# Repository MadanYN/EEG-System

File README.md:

# EEG-System
The aim of the project is to develop an ELectroencephalogram(EEG) Acquisition System that
is capable of monitoring brain activity through 24 different channels simultaneously. The system should convey the captured data in real-time to a computer over Bluetooth and the receiver should plot waveforms of all the channels. The design is inspired by the OpenBCI Cyton/Ganglion biosensing board, which is a well-known and widely used EEG system.

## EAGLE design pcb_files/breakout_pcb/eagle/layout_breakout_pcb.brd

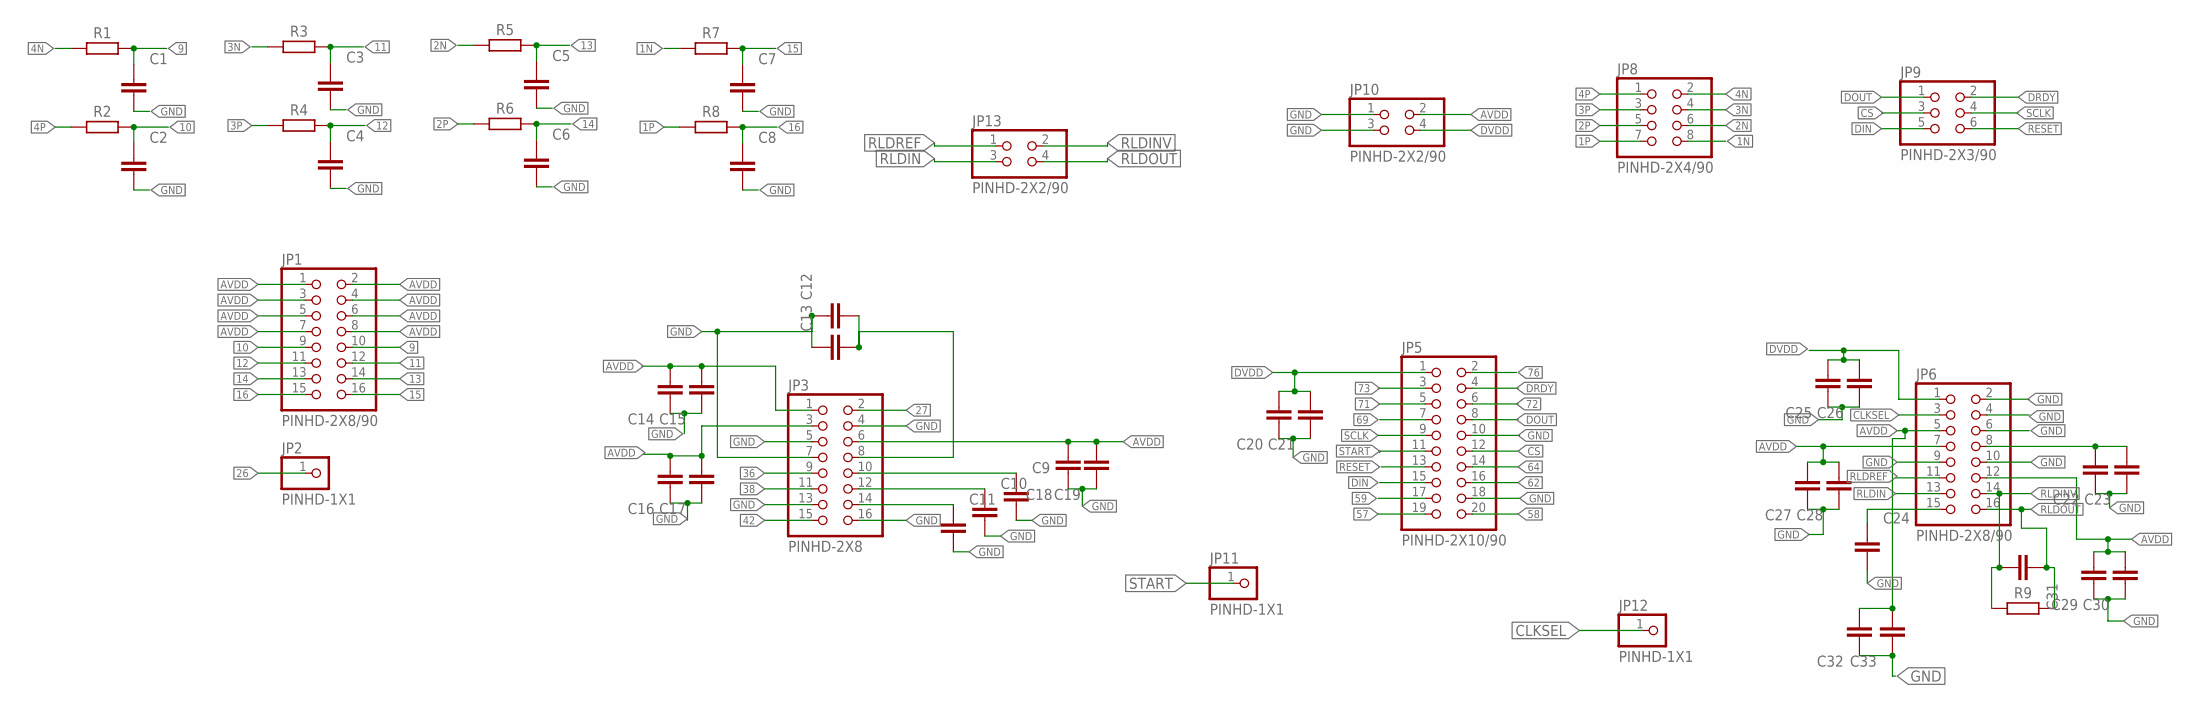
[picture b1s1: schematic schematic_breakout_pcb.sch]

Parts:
C1, C2, C3, C4, C5, C6, C7, C8, C9, C10, C11, C12, C13, C14, C15, C16, C17, C18, C19, C20, C21, C22, C23, C24, C25, C26, C27, C28, C29, C30, C31, C32, C33: C_TANTALUM-1206(3216-METRIC); CAPM3216X180
JP1, JP6: PINHD-2X8/90; 2X08/90
JP2, JP11, JP12: PINHD-1X1; 1X01
JP3: PINHD-2X8; 2X08
JP5: PINHD-2X10/90; 2X10/90
JP8: PINHD-2X4/90; 2X04/90
JP9: PINHD-2X3/90; 2X03/90
JP10, JP13: PINHD-2X2/90; 2X02/90
R1, R2, R3, R4, R5, R6, R7, R8, R9: R_CHIP-1206(3216-METRIC); RESC3216X70

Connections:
1N: JP8.8, R7.1
1P: JP8.7, R8.1
2N: JP8.6, R5.1
2P: JP8.5, R6.1
3N: JP8.4, R3.1
3P: JP8.3, R4.1
4N: JP8.2, R1.1
4P: JP8.1, R2.1
9: C1.1, JP1.10, R1.2
10: C2.1, JP1.9, R2.2
11: C3.1, JP1.12, R3.2
12: C4.1, JP1.11, R4.2
13: C5.1, JP1.14, R5.2
14: C6.1, JP1.13, R6.2
15: C7.1, JP1.16, R7.2
16: C8.1, JP1.15, R8.2
26: JP2.1
27: JP3.2
36: JP3.9
38: JP3.11
42: JP3.15
57: JP5.19
58: JP5.20
59: JP5.17
62: JP5.16
64: JP5.14
69: JP5.7
71: JP5.5
72: JP5.6
73: JP5.3
76: JP5.2
AVDD: C14.2, C15.2, C16.2, C17.2, C18.2, C19.2, C27.2, C28.2, C29.2, C30.2, C32.2, C33.2, JP1.1, JP1.2, JP1.3, JP1.4, JP1.5, JP1.6, JP1.7, JP1.8, JP3.1, JP3.3, JP3.6, JP6.5, JP6.7, JP6.12, JP10.2
CLKSEL: JP6.3, JP12.1
CS: JP5.12, JP9.3
DIN: JP5.15, JP9.5
DOUT: JP5.8, JP9.1
DRDY: JP5.4, JP9.2
DVDD: C20.2, C21.2, C25.2, C26.2, JP5.1, JP6.1, JP10.4
GND: C1.2, C2.2, C3.2, C4.2, C5.2, C6.2, C7.2, C8.2, C9.2, C10.2, C11.2, C12.1, C13.1, C14.1, C15.1, C16.1, C17.1, C18.1, C19.1, C20.1, C21.1, C22.1, C23.1, C24.2, C25.1, C26.1, C27.1, C28.1, C29.1, C30.1, C32.1, C33.1, JP3.4, JP3.5, JP3.7, JP3.13, JP3.16, JP5.10, JP5.18, JP6.2, JP6.4, JP6.6, JP6.9, JP6.10, JP10.1, JP10.3
unnamed: C9.1, JP3.10
unnamed: C10.1, JP3.12
unnamed: C11.1, JP3.14
unnamed: C12.2, C13.2, JP3.8
unnamed: C22.2, C23.2, JP6.8
unnamed: C24.1, JP6.15
RESET: JP5.13, JP9.6
RLDIN: JP6.13, JP13.3
RLDINV: C31.2, JP6.14, JP13.2, R9.1
RLDOUT: C31.1, JP6.16, JP13.4, R9.2
RLDREF: JP6.11, JP13.1
SCLK: JP5.9, JP9.4
START: JP5.11, JP11.1

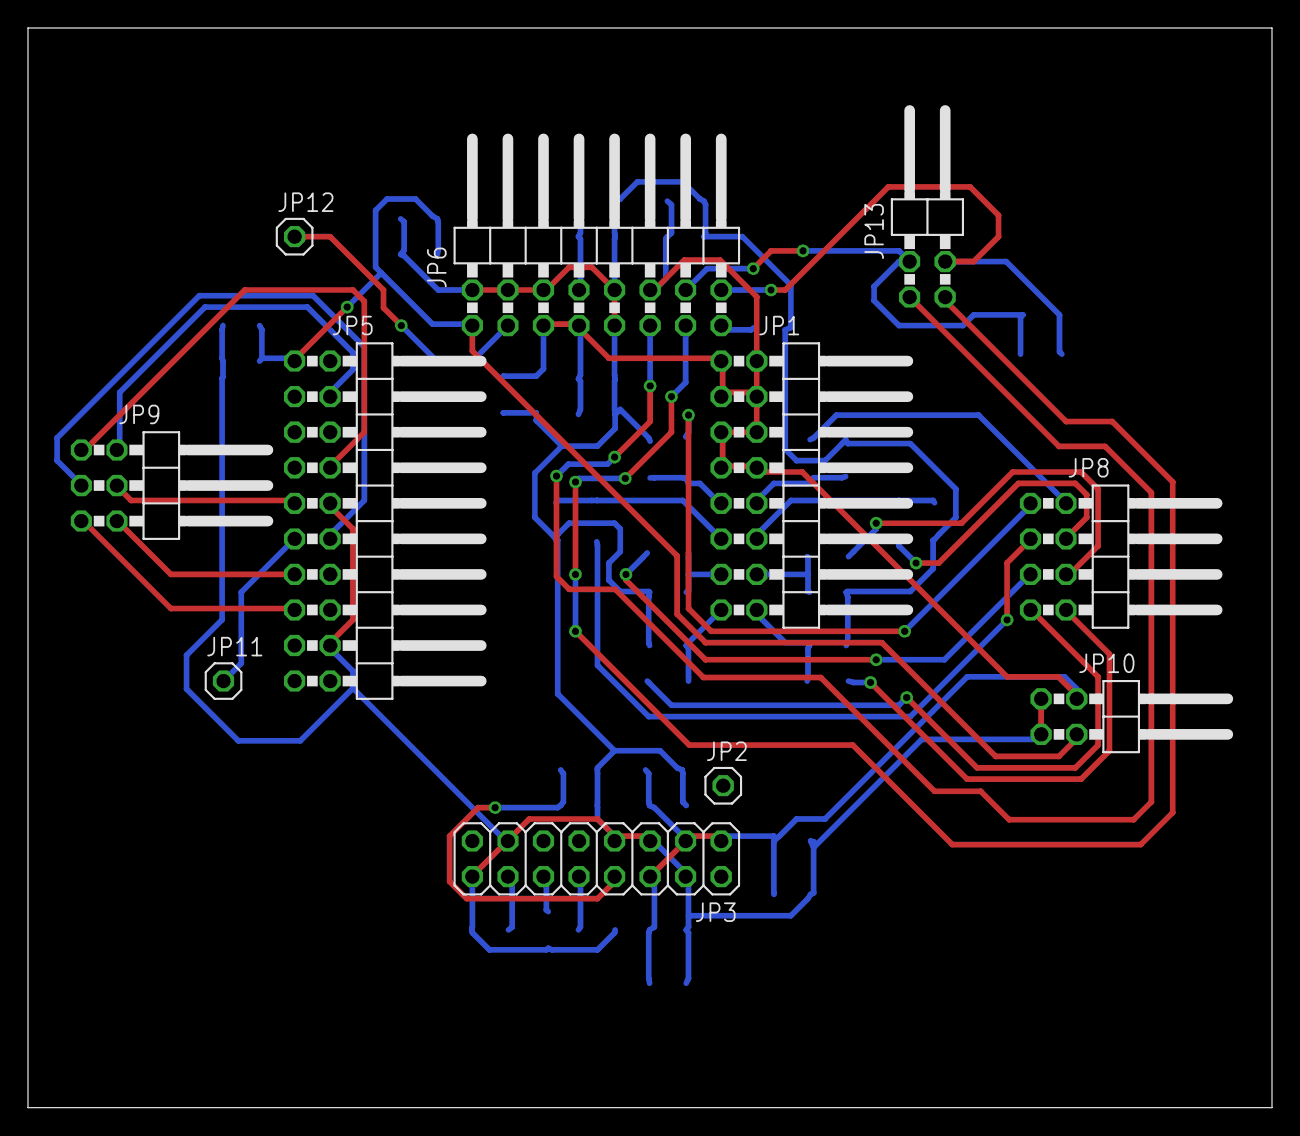
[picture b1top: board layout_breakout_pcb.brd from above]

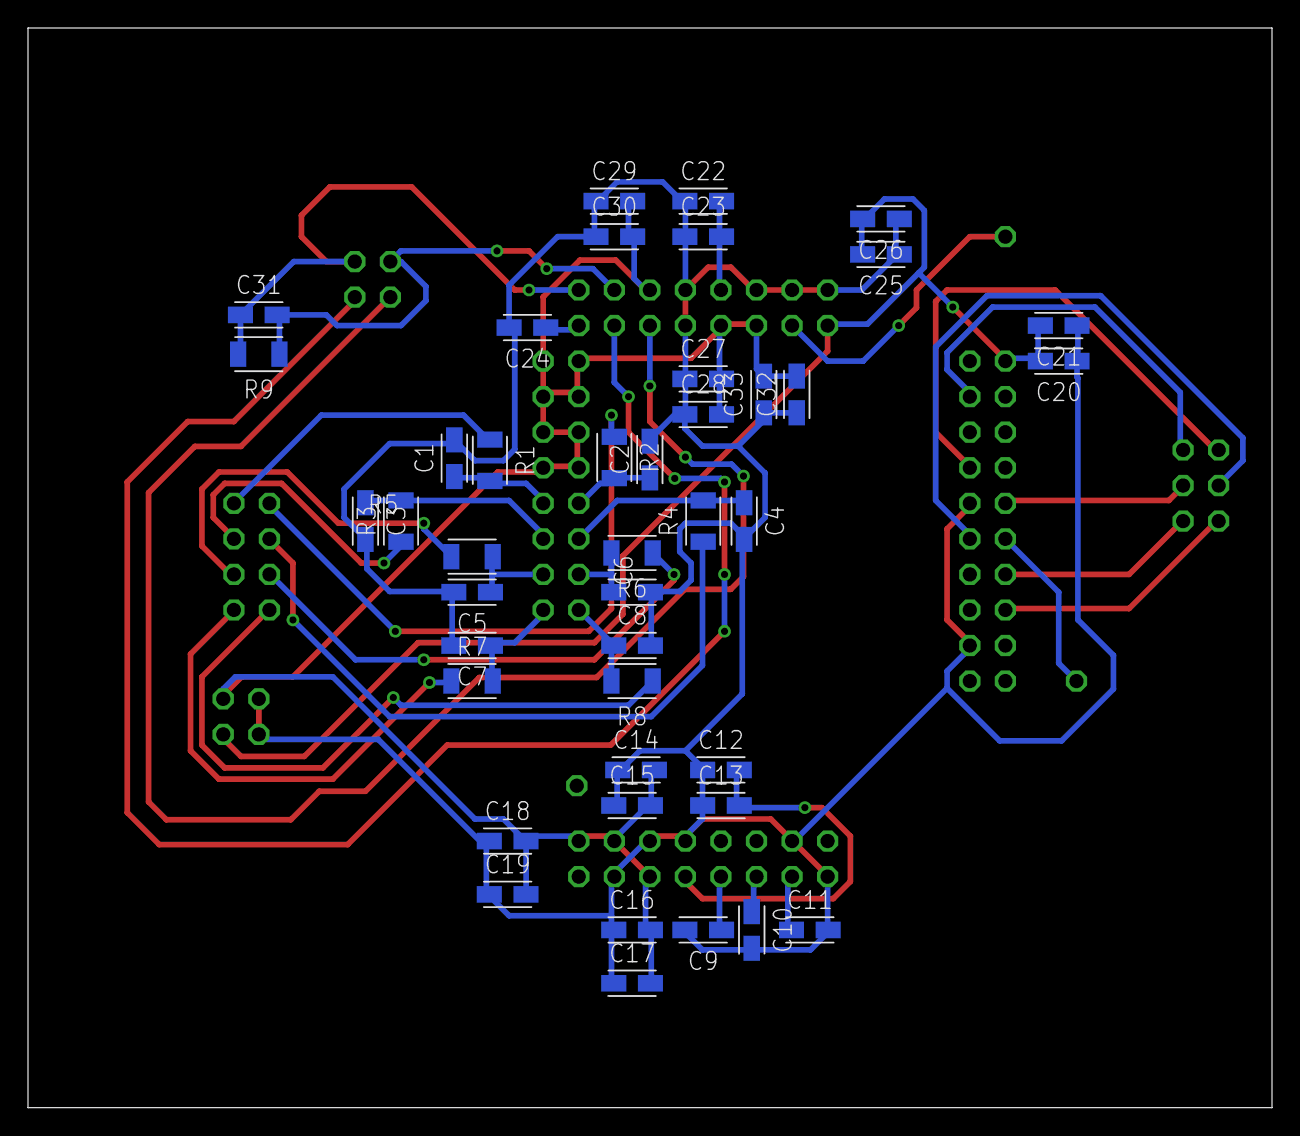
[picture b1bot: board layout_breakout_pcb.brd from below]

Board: 2 copper layers, 88.9 x 77.1 mm, 53 parts (42 on the bottom side), 37 nets.

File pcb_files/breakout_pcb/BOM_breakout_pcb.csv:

"Part";"Value";"Device";"Package";"Description";"CATEGORY";"DESCRIPTION";"MANUFACTURER";"MPN";"OPERATING_TEMP";"PART_STATUS";"RATING";"ROHS_COMPLIANT";"SERIES";"SUB-CATEGORY";"THERMALLOSS";"TOLERANCE";"TYPE";"VOLTAGE_RATING";
"C1";"";"C_TANTALUM-1206(3216-METRIC)";"CAPM3216X180";"Capacitor - Generic";"Capacitor";"";"";"";"";"";"";"";"";"";"";"";"";"";
"C2";"";"C_TANTALUM-1206(3216-METRIC)";"CAPM3216X180";"Capacitor - Generic";"Capacitor";"";"";"";"";"";"";"";"";"";"";"";"";"";
"C3";"";"C_TANTALUM-1206(3216-METRIC)";"CAPM3216X180";"Capacitor - Generic";"Capacitor";"";"";"";"";"";"";"";"";"";"";"";"";"";
"C4";"";"C_TANTALUM-1206(3216-METRIC)";"CAPM3216X180";"Capacitor - Generic";"Capacitor";"";"";"";"";"";"";"";"";"";"";"";"";"";
"C5";"";"C_TANTALUM-1206(3216-METRIC)";"CAPM3216X180";"Capacitor - Generic";"Capacitor";"";"";"";"";"";"";"";"";"";"";"";"";"";
"C6";"";"C_TANTALUM-1206(3216-METRIC)";"CAPM3216X180";"Capacitor - Generic";"Capacitor";"";"";"";"";"";"";"";"";"";"";"";"";"";
"C7";"";"C_TANTALUM-1206(3216-METRIC)";"CAPM3216X180";"Capacitor - Generic";"Capacitor";"";"";"";"";"";"";"";"";"";"";"";"";"";
"C8";"";"C_TANTALUM-1206(3216-METRIC)";"CAPM3216X180";"Capacitor - Generic";"Capacitor";"";"";"";"";"";"";"";"";"";"";"";"";"";
"C9";"";"C_TANTALUM-1206(3216-METRIC)";"CAPM3216X180";"Capacitor - Generic";"Capacitor";"";"";"";"";"";"";"";"";"";"";"";"";"";
"C10";"";"C_TANTALUM-1206(3216-METRIC)";"CAPM3216X180";"Capacitor - Generic";"Capacitor";"";"";"";"";"";"";"";"";"";"";"";"";"";
"C11";"";"C_TANTALUM-1206(3216-METRIC)";"CAPM3216X180";"Capacitor - Generic";"Capacitor";"";"";"";"";"";"";"";"";"";"";"";"";"";
"C12";"";"C_TANTALUM-1206(3216-METRIC)";"CAPM3216X180";"Capacitor - Generic";"Capacitor";"";"";"";"";"";"";"";"";"";"";"";"";"";
"C13";"";"C_TANTALUM-1206(3216-METRIC)";"CAPM3216X180";"Capacitor - Generic";"Capacitor";"";"";"";"";"";"";"";"";"";"";"";"";"";
"C14";"";"C_TANTALUM-1206(3216-METRIC)";"CAPM3216X180";"Capacitor - Generic";"Capacitor";"";"";"";"";"";"";"";"";"";"";"";"";"";
"C15";"";"C_TANTALUM-1206(3216-METRIC)";"CAPM3216X180";"Capacitor - Generic";"Capacitor";"";"";"";"";"";"";"";"";"";"";"";"";"";
"C16";"";"C_TANTALUM-1206(3216-METRIC)";"CAPM3216X180";"Capacitor - Generic";"Capacitor";"";"";"";"";"";"";"";"";"";"";"";"";"";
"C17";"";"C_TANTALUM-1206(3216-METRIC)";"CAPM3216X180";"Capacitor - Generic";"Capacitor";"";"";"";"";"";"";"";"";"";"";"";"";"";
"C18";"";"C_TANTALUM-1206(3216-METRIC)";"CAPM3216X180";"Capacitor - Generic";"Capacitor";"";"";"";"";"";"";"";"";"";"";"";"";"";
"C19";"";"C_TANTALUM-1206(3216-METRIC)";"CAPM3216X180";"Capacitor - Generic";"Capacitor";"";"";"";"";"";"";"";"";"";"";"";"";"";
"C20";"";"C_TANTALUM-1206(3216-METRIC)";"CAPM3216X180";"Capacitor - Generic";"Capacitor";"";"";"";"";"";"";"";"";"";"";"";"";"";
"C21";"";"C_TANTALUM-1206(3216-METRIC)";"CAPM3216X180";"Capacitor - Generic";"Capacitor";"";"";"";"";"";"";"";"";"";"";"";"";"";
"C22";"";"C_TANTALUM-1206(3216-METRIC)";"CAPM3216X180";"Capacitor - Generic";"Capacitor";"";"";"";"";"";"";"";"";"";"";"";"";"";
"C23";"";"C_TANTALUM-1206(3216-METRIC)";"CAPM3216X180";"Capacitor - Generic";"Capacitor";"";"";"";"";"";"";"";"";"";"";"";"";"";
"C24";"";"C_TANTALUM-1206(3216-METRIC)";"CAPM3216X180";"Capacitor - Generic";"Capacitor";"";"";"";"";"";"";"";"";"";"";"";"";"";
"C25";"";"C_TANTALUM-1206(3216-METRIC)";"CAPM3216X180";"Capacitor - Generic";"Capacitor";"";"";"";"";"";"";"";"";"";"";"";"";"";
"C26";"";"C_TANTALUM-1206(3216-METRIC)";"CAPM3216X180";"Capacitor - Generic";"Capacitor";"";"";"";"";"";"";"";"";"";"";"";"";"";
"C27";"";"C_TANTALUM-1206(3216-METRIC)";"CAPM3216X180";"Capacitor - Generic";"Capacitor";"";"";"";"";"";"";"";"";"";"";"";"";"";
"C28";"";"C_TANTALUM-1206(3216-METRIC)";"CAPM3216X180";"Capacitor - Generic";"Capacitor";"";"";"";"";"";"";"";"";"";"";"";"";"";
"C29";"";"C_TANTALUM-1206(3216-METRIC)";"CAPM3216X180";"Capacitor - Generic";"Capacitor";"";"";"";"";"";"";"";"";"";"";"";"";"";
"C30";"";"C_TANTALUM-1206(3216-METRIC)";"CAPM3216X180";"Capacitor - Generic";"Capacitor";"";"";"";"";"";"";"";"";"";"";"";"";"";
"C31";"";"C_TANTALUM-1206(3216-METRIC)";"CAPM3216X180";"Capacitor - Generic";"Capacitor";"";"";"";"";"";"";"";"";"";"";"";"";"";
"C32";"";"C_TANTALUM-1206(3216-METRIC)";"CAPM3216X180";"Capacitor - Generic";"Capacitor";"";"";"";"";"";"";"";"";"";"";"";"";"";
"C33";"";"C_TANTALUM-1206(3216-METRIC)";"CAPM3216X180";"Capacitor - Generic";"Capacitor";"";"";"";"";"";"";"";"";"";"";"";"";"";
"JP1";"PINHD-2X8/90";"PINHD-2X8/90";"2X08/90";"PIN HEADER";"CONNECTOR";"";"";"";"";"";"";"";"";"PIN-HEADER";"";"";"";"";
"JP2";"PINHD-1X1";"PINHD-1X1";"1X01";"PIN HEADER";"CONNECTOR";"";"";"";"";"";"";"";"";"PIN-HEADER";"";"";"";"";
"JP3";"PINHD-2X8";"PINHD-2X8";"2X08";"PIN HEADER";"CONNECTOR";"";"";"";"";"";"";"";"";"PIN-HEADER";"";"";"";"";
"JP5";"PINHD-2X10/90";"PINHD-2X10/90";"2X10/90";"PIN HEADER";"CONNECTOR";"";"";"";"";"";"";"";"";"PIN-HEADER";"";"";"";"";
"JP6";"PINHD-2X8/90";"PINHD-2X8/90";"2X08/90";"PIN HEADER";"CONNECTOR";"";"";"";"";"";"";"";"";"PIN-HEADER";"";"";"";"";
"JP8";"PINHD-2X4/90";"PINHD-2X4/90";"2X04/90";"PIN HEADER";"CONNECTOR";"";"";"";"";"";"";"";"";"PIN-HEADER";"";"";"";"";
"JP9";"PINHD-2X3/90";"PINHD-2X3/90";"2X03/90";"PIN HEADER";"CONNECTOR";"";"";"";"";"";"";"";"";"PIN-HEADER";"";"";"";"";
"JP10";"PINHD-2X2/90";"PINHD-2X2/90";"2X02/90";"PIN HEADER";"CONNECTOR";"";"";"";"";"";"";"";"";"PIN-HEADER";"";"";"";"";
"JP11";"PINHD-1X1";"PINHD-1X1";"1X01";"PIN HEADER";"CONNECTOR";"";"";"";"";"";"";"";"";"PIN-HEADER";"";"";"";"";
"JP12";"PINHD-1X1";"PINHD-1X1";"1X01";"PIN HEADER";"CONNECTOR";"";"";"";"";"";"";"";"";"PIN-HEADER";"";"";"";"";
"JP13";"PINHD-2X2/90";"PINHD-2X2/90";"2X02/90";"PIN HEADER";"CONNECTOR";"";"";"";"";"";"";"";"";"PIN-HEADER";"";"";"";"";
"R1";"";"R_CHIP-1206(3216-METRIC)";"RESC3216X70";"Resistor Fixed - Generic";"Resistor";"";"";"";"";"";"";"";"";"Fixed";"";"";"";"";
"R2";"";"R_CHIP-1206(3216-METRIC)";"RESC3216X70";"Resistor Fixed - Generic";"Resistor";"";"";"";"";"";"";"";"";"Fixed";"";"";"";"";
"R3";"";"R_CHIP-1206(3216-METRIC)";"RESC3216X70";"Resistor Fixed - Generic";"Resistor";"";"";"";"";"";"";"";"";"Fixed";"";"";"";"";
"R4";"";"R_CHIP-1206(3216-METRIC)";"RESC3216X70";"Resistor Fixed - Generic";"Resistor";"";"";"";"";"";"";"";"";"Fixed";"";"";"";"";
"R5";"";"R_CHIP-1206(3216-METRIC)";"RESC3216X70";"Resistor Fixed - Generic";"Resistor";"";"";"";"";"";"";"";"";"Fixed";"";"";"";"";
"R6";"";"R_CHIP-1206(3216-METRIC)";"RESC3216X70";"Resistor Fixed - Generic";"Resistor";"";"";"";"";"";"";"";"";"Fixed";"";"";"";"";
"R7";"";"R_CHIP-1206(3216-METRIC)";"RESC3216X70";"Resistor Fixed - Generic";"Resistor";"";"";"";"";"";"";"";"";"Fixed";"";"";"";"";
"R8";"";"R_CHIP-1206(3216-METRIC)";"RESC3216X70";"Resistor Fixed - Generic";"Resistor";"";"";"";"";"";"";"";"";"Fixed";"";"";"";"";
"R9";"";"R_CHIP-1206(3216-METRIC)";"RESC3216X70";"Resistor Fixed - Generic";"Resistor";"";"";"";"";"";"";"";"";"Fixed";"";"";"";"";

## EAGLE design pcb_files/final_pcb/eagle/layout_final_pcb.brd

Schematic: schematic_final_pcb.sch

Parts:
C1, C2, C6, C8, C9, C11, C13, C16, C20, C23, C27, C29, C32, C37, C40, C44, C46, C49, C53, C56, C57, C59, C62, C65, C70, C72, C75, C78, C79, C80, C82, C88, C90, C92, C95, C99, C105, C111, C112, C113, C116, C117, C123, C124, C133, C134, C135, C137, C143, C150, C151, C155, C157, C159, C161, C163, C165, C167, C169, C171, C173, C175, C177, C179, C181, C183, C185, C187, C189, C191, C193, C195, C197, C199, C201, C203, C205, C207, C209, C211, C213, C215, C217, C219, C221, C223, C225, C227, C229, C231, C233, C235, C237, C239, C241, C243, C245, C247, C250, C252, C254, C256, C258: 0.1uF; CAPC2012X110
C3, C4, C10, C12, C15, C17, C19, C22, C26, C28, C31, C33, C34, C36, C38, C39, C43, C45, C48, C50, C52, C55, C58, C61, C63, C66, C69, C71, C74, C76, C81, C91, C97, C118, C119, C120, C121, C125, C138, C139, C140, C141, C142, C144, C145, C146, C147, C148, C149, C152, C156, C158, C160, C162, C164, C166, C168, C170, C172, C174, C176, C178, C180, C182, C184, C186, C188, C190, C192, C194, C196, C198, C200, C202, C204, C206, C208, C210, C212, C214, C216, C218, C220, C222, C224, C226, C228, C230, C232, C234, C236, C238, C240, C242, C244, C246, C248, C251, C253, C255, C257, C259: 1uF; CAPC2012X110
C5, C14, C18, C30, C35, C47, C51, C60, C64, C73, C77, C85, C86: 10uF; CAP_293D-A_VSS
C7, C25, C42, C68, C84, C94: 100pF; CAPC1608X85
C21, C87, C89, C96, C100, C132: 2.2uF; CAPC1608X85
C24, C41, C54, C67, C83, C93: 1.5nF; CAPC1608X85
C98: 0.01uF; CAPC2012X110
C101, C102, C122, C136, C153, C154: 22uF; CAPM3216X180
C103, C104, C106, C107, C108, C109, C110, C126, C127, C128, C129, C130, C131: CKCL44X7R1H102M085AACKCL44_TDK-L; CKCL44_TDK-L
C114, C115: 15pF; CAPC1608X85
CR1: BAT85,113DO-34_NEX; DO-34_NEX
FB1, FB2, FB3, FB4, FB5, FB6, FB7, FB8, FB9, FB10, FB11, FB12, FB13, FB14: FERRITE_BEAD; BEADC1608X95N
J1: 3A/250V; B2B-XH-A
JP1, JP5: PINHD-1X6/90; 1X06/90
JP3, JP16, JP18: PINHD-2X3/90; 2X03/90
JP4, JP6: PINHD-1X8/90; 1X08/90
JP7: PINHD-1X7/90; 1X07/90
JP9, JP11, JP13, JP14, JP15, JP17: PINHD-2X4/90; 2X04/90
JP10: PINHD-1X4; 1X04
JP12: PINHD-1X1; 1X01
JP19, JP20, JP21, JP22, JP23, JP24: PINHD-1X2/90; 1X02/90
R1: 1k; RESC1608X60
R2: 470k; RESC1608X60
R3, R4, R5, R6, R7, R8, R10: 1M; RESC1608X60
R9: 10k; RESC1608X60
RN1, RN2, RN3, RN4, RN5, RN6, RN7, RN8, RN9, RN10, RN11, RN12, RN13: CAY16-2201F4LF; RESCAF80P320X160X60-8N
S2: B3U-X000B3U3000P(M)-B3000P(M)-B; B3U-3000P(M)-B
TP1, TP4, TP5, TP7, TP8, TP9, TP10, TP16, TP18, TP19, TP20, TP21, TP22, TP23, TP24, TP25, TP26, TP27, TP28, TP29, TP30: TP; 1X01
TPCS1, TPCS2, TPCS3, TPCS4, TPCS5, TPCS6, TPCS7, TPCS8, TPCS9: TP; 1X01
TPRAW: TP; 1X01
U1, U2, U3, U4, U5, U7: ADS1194CPAG; QFP50P1200X1200X120-64N
U6: LM2664M6; SOT95P280X145-6N
U8: PIC32MX250F128D-I_PT; QFP44_10X10MC
U9: MCP1754T-5002E/MC; SON50P200X300X100-9N
U10: TPS72325QDBVRQ1; SOT95P280X145-5N
U11: TLV70012QDCKRQ1; SOT65P210X110-5N
U13, U14, U15, U16, U17, U18, U19, U20, U21, U22, U23, U24, U25: TPD4E1B06DRLR; SOT50P160X60-6N
U26: LIS3DHHTRQFN_ICLX_STM; QFN_ICLX_STM
XTAL1: 8M; XTALRR488W45L1150T500H350B

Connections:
1N: JP17.7, RN1.3, U13.1 (IO1)
1P: JP17.8, RN1.4, U13.3 (IO2)
2N: JP17.5, RN1.1, U13.4 (IO3)
2P: JP17.6, RN1.2, U13.6 (IO4)
3N: JP17.3, RN2.3, U14.1 (IO1)
3P: JP17.4, RN2.4, U14.3 (IO2)
4N: JP17.1, RN2.1, U14.4 (IO3)
4P: JP17.2, RN2.2, U14.6 (IO4)
5N: JP18.5, RN3.3, U15.1 (IO1)
5P: JP18.6, RN3.4, U15.3 (IO2)
6N: JP18.3, RN3.1, U15.4 (IO3)
6P: JP18.4, RN3.2, U15.6 (IO4)
7N: JP18.1, RN4.3, U16.1 (IO1)
7P: JP18.2, RN4.4, U16.3 (IO2)
8N: JP9.7, RN4.1, U16.4 (IO3)
8P: JP9.8, RN4.2, U16.6 (IO4)
9N: JP15.7, RN5.3, U17.1 (IO1)
9P: JP15.8, RN5.4, U17.3 (IO2)
10N: JP15.5, RN5.1, U17.4 (IO3)
10P: JP15.6, RN5.2, U17.6 (IO4)
11N: JP15.3, RN6.3, U18.1 (IO1)
11P: JP15.4, RN6.4, U18.3 (IO2)
12N: JP15.1, RN6.1, U18.4 (IO3)
12P: JP15.2, RN6.2, U18.6 (IO4)
13N: JP16.5, RN7.3, U19.1 (IO1)
13P: JP16.6, RN7.4, U19.3 (IO2)
14N: JP16.3, RN7.1, U19.4 (IO3)
14P: JP16.4, RN7.2, U19.6 (IO4)
15N: JP16.1, RN8.3, U20.1 (IO1)
15P: JP16.2, RN8.4, U20.3 (IO2)
16N: JP11.7, RN8.1, U20.4 (IO3)
16P: JP11.8, RN8.2, U20.6 (IO4)
17N: JP14.7, RN9.3, U21.1 (IO1)
17P: JP14.8, RN9.4, U21.3 (IO2)
18N: JP14.5, RN9.1, U21.4 (IO3)
18P: JP14.6, RN9.2, U21.6 (IO4)
19N: JP14.3, RN10.3, U22.1 (IO1)
19P: JP14.4, RN10.4, U22.3 (IO2)
20N: JP14.1, RN10.1, U22.4 (IO3)
20P: JP14.2, RN10.2, U22.6 (IO4)
21N: JP3.5, RN11.3, U23.1 (IO1)
21P: JP3.6, RN11.4, U23.3 (IO2)
22N: JP3.3, RN11.1, U23.4 (IO3)
22P: JP3.4, RN11.2, U23.6 (IO4)
23N: JP3.1, RN12.3, U24.1 (IO1)
23P: JP3.2, RN12.4, U24.3 (IO2)
24N: JP13.7, RN12.1, U24.4 (IO3)
24P: JP13.8, RN12.2, U24.6 (IO4)
-RAW: C51.2, C89.1, U6.2 (OUT), U10.1 (IN), U10.2 (EN)
AGND: C1.2, C6.2, C11.2, C12.2, C18.1, C19.2, C20.2, C27.2, C28.2, C35.1, C36.2, C37.2, C38.2, C44.2, C45.2, C51.1, C52.2, C53.2, C57.2, C58.2, C65.2, C66.2, C70.2, C71.2, C78.2, C79.2, C80.2, C87.2, C89.2, C90.2, C95.2, C96.2, C97.2, C98.2, C99.2, C100.2, C103.1, C103.2, C103.3, C103.4, C104.1, C104.2, C104.3, C104.4, C105.2, C106.1, C106.2, C106.3, C106.4, C107.1, C107.2, C107.3, C107.4, C108.1, C108.2, C108.3, C108.4, C109.1, C109.2, C109.3, C109.4, C110.1, C110.2, C110.3, C110.4, C112.1, C116.2, C118.2, C120.2, C123.2, C124.2, C125.2, C126.1, C126.2, C126.3, C126.4, C127.1, C127.2, C127.3, C127.4, C128.1, C128.2, C128.3, C128.4, C129.1, C129.2, C129.3, C129.4, C130.1, C130.2, C130.3, C130.4, C131.1, C131.2, C131.3, C131.4, C131.6, C131.7, C131.8, C132.2, C133.2, C134.2, C135.2, C137.2, C138.2, C139.2, C140.2, C141.2, C142.2, C143.2, C144.2, C145.2, C146.2, C147.2, C148.2, C149.2, C152.2, C155.2, C156.2, C157.2, C158.2, C159.2, C160.2, C161.2, C162.2, C163.2, C164.2, C165.2, C166.2, C169.2, C170.2, C171.2, C172.2, C173.2, C174.2, C175.2, C176.2, C177.2, C178.2, C179.2, C180.2, C181.2, C182.2, C183.2, C184.2, C185.2, C186.2, C187.2, C188.2, C189.2, C190.2, C191.2, C192.2, C193.2, C194.2, C195.2, C196.2, C197.2, C198.2, C199.2, C200.2, C201.2, C202.2, C203.2, C204.2, C205.2, C206.2, C207.2, C208.2, C209.2, C210.2, C211.2, C212.2, C213.2, C214.2, C215.2, C216.2, C217.2, C218.2, C219.2, C220.2, C221.2, C222.2, C223.2, C224.2, C225.2, C226.2, C227.2, C228.2, C229.2, C230.2, C231.2, C232.2, C233.2, C234.2, C235.2, C236.2, C237.2, C238.2, C239.2, C240.2, C241.2, C242.2, C243.2, C244.2, C245.2, C246.2, C247.2, C248.2, FB1.1, FB2.1, FB3.1, FB4.1, FB5.1, FB6.1, FB7.1, FB8.1, FB9.1, FB10.1, FB11.1, FB12.1, FB13.1, FB14.1, J1.2, JP5.4, JP7.3, JP9.3, JP9.4, JP11.3, JP11.4, JP13.3, JP13.4, RN13.2, RN13.3, RN13.4, RN13.5, RN13.6, RN13.7, TP18.1, TP19.1, TP20.1, TP21.1, U6.1 (GND), U8.16 (AVSS), U9.4 (GND), U10.3 (GND), U11.2 (GND), U13.2 (GND), U14.2 (GND), U15.2 (GND), U16.2 (GND), U17.2 (GND), U18.2 (GND), U19.2 (GND), U20.2 (GND), U21.2 (GND), U22.2 (GND), U23.2 (GND), U24.2 (GND), U25.2 (GND), U25.4 (IO3)
AVDD: C1.1, C11.1, C12.1, C18.2, C27.1, C28.1, C44.1, C45.1, C57.1, C58.1, C70.1, C71.1, C100.1, C116.1, C120.1, C133.1, C134.1, C135.1, C137.1, C143.1, C144.1, C145.1, C146.1, C147.1, C148.1, C149.1, C159.1, C160.1, C161.1, C162.1, C163.1, C164.1, C165.1, C166.1, C209.1, C210.1, C211.1, C212.1, C213.1, C214.1, C215.1, C216.1, C217.1, C218.1, C219.1, C220.1, C221.1, C222.1, C223.1, C224.1, C225.1, C226.1, C227.1, C228.1, C229.1, C230.1, C231.1, C232.1, C233.1, C234.1, C235.1, C236.1, C237.1, C238.1, C239.1, C240.1, C241.1, C242.1, C243.1, C244.1, C245.1, C246.1, C247.1, C248.1, JP9.1, JP9.2, JP11.1, JP11.2, JP13.1, JP13.2, TP1.1, U1.1 (IN8N), U1.2 (IN8P), U1.3 (IN7N), U1.4 (IN7P), U1.5 (IN6N), U1.6 (IN6P), U1.7 (IN5N), U1.8 (IN5P), U1.19 (AVDD), U1.21 (AVDD), U1.22 (AVDD), U1.54 (AVDD1), U1.56 (AVDD), U1.59 (AVDD), U2.1 (IN8N), U2.2 (IN8P), U2.3 (IN7N), U2.4 (IN7P), U2.5 (IN6N), U2.6 (IN6P), U2.7 (IN5N), U2.8 (IN5P), U2.19 (AVDD), U2.21 (AVDD), U2.22 (AVDD), U2.54 (AVDD1), U2.56 (AVDD), U2.59 (AVDD), U3.1 (IN8N), U3.2 (IN8P), U3.3 (IN7N), U3.4 (IN7P), U3.5 (IN6N), U3.6 (IN6P), U3.7 (IN5N), U3.8 (IN5P), U3.19 (AVDD), U3.21 (AVDD), U3.22 (AVDD), U3.54 (AVDD1), U3.56 (AVDD), U3.59 (AVDD), U4.1 (IN8N), U4.2 (IN8P), U4.3 (IN7N), U4.4 (IN7P), U4.5 (IN6N), U4.6 (IN6P), U4.7 (IN5N), U4.8 (IN5P), U4.19 (AVDD), U4.21 (AVDD), U4.22 (AVDD), U4.54 (AVDD1), U4.56 (AVDD), U4.59 (AVDD), U5.1 (IN8N), U5.2 (IN8P), U5.3 (IN7N), U5.4 (IN7P), U5.5 (IN6N), U5.6 (IN6P), U5.7 (IN5N), U5.8 (IN5P), U5.19 (AVDD), U5.21 (AVDD), U5.22 (AVDD), U5.54 (AVDD1), U5.56 (AVDD), U5.59 (AVDD), U7.1 (IN8N), U7.2 (IN8P), U7.3 (IN7N), U7.4 (IN7P), U7.5 (IN6N), U7.6 (IN6P), U7.7 (IN5N), U7.8 (IN5P), U7.19 (AVDD), U7.21 (AVDD), U7.22 (AVDD), U7.54 (AVDD1), U7.56 (AVDD), U7.59 (AVDD), U11.5 (OUT), U25.3 (IO2)
AVSS: C2.1, C3.2, C5.2, C6.1, C7.2, C8.2, C10.2, C13.1, C14.2, C15.2, C16.2, C17.2, C19.1, C20.1, C25.2, C26.2, C29.1, C30.2, C31.2, C32.2, C33.2, C34.2, C35.2, C36.1, C37.1, C38.1, C42.2, C43.2, C46.1, C47.2, C48.2, C49.2, C50.2, C52.1, C53.1, C59.1, C60.2, C61.2, C62.2, C63.2, C65.1, C66.1, C68.2, C69.2, C72.1, C73.2, C74.2, C75.2, C76.2, C78.1, C79.1, C80.1, C84.2, C90.1, C94.2, C95.1, C96.1, C97.1, C99.1, C101.2, C102.2, C105.1, C118.1, C119.2, C121.2, C122.2, C123.1, C124.1, C125.1, C136.2, C138.1, C139.1, C140.1, C141.1, C142.1, C152.1, C153.2, C154.2, C155.1, C156.1, C157.1, C158.1, C169.1, C170.1, C171.1, C172.1, C173.1, C174.1, C175.1, C176.1, C177.1, C178.1, C179.1, C180.1, C181.1, C182.1, C183.1, C184.1, C185.1, C186.1, C187.1, C188.1, C189.1, C190.1, C191.1, C192.1, C193.1, C194.1, C195.1, C196.1, C197.1, C198.1, C199.1, C200.1, C201.1, C202.1, C203.1, C204.1, C205.1, C206.1, C207.1, C208.1, TP8.1, U1.20 (AVSS), U1.23 (AVSS), U1.25 (VREFN), U1.32 (AVSS), U1.53 (AVSS1), U1.57 (AVSS), U1.58 (AVSS), U2.20 (AVSS), U2.23 (AVSS), U2.25 (VREFN), U2.32 (AVSS), U2.53 (AVSS1), U2.57 (AVSS), U2.58 (AVSS), U3.20 (AVSS), U3.23 (AVSS), U3.25 (VREFN), U3.32 (AVSS), U3.53 (AVSS1), U3.57 (AVSS), U3.58 (AVSS), U4.20 (AVSS), U4.23 (AVSS), U4.25 (VREFN), U4.32 (AVSS), U4.53 (AVSS1), U4.57 (AVSS), U4.58 (AVSS), U5.20 (AVSS), U5.23 (AVSS), U5.25 (VREFN), U5.32 (AVSS), U5.53 (AVSS1), U5.57 (AVSS), U5.58 (AVSS), U7.20 (AVSS), U7.23 (AVSS), U7.25 (VREFN), U7.32 (AVSS), U7.53 (AVSS1), U7.57 (AVSS), U7.58 (AVSS), U10.4 (OUT), U25.1 (IO1)
BIAS: JP9.5, JP9.6, JP11.5, JP11.6, JP13.5, JP13.6, RN13.1, U25.6 (IO4)
BIAS_ESD: C131.5, RN13.8, U1.60 (RLDREF), U2.60 (RLDREF), U3.60 (RLDREF), U4.60 (RLDREF), U5.60 (RLDREF), U7.60 (RLDREF)
BOOT_EN: R2.2, S2.1, U8.33 (SOSCI/RPB4/RB4)
CLK: JP6.6, JP12.1, U1.37 (CLK), U2.37 (CLK), U3.37 (CLK), U4.37 (CLK), U5.37 (CLK), U7.37 (CLK)
CS1: TPCS1.1, U4.39 (!CS), U8.15 (AN9/C3INA/RPB15/SCK2/CTED6/PMCS1/RB15)
CS2: TPCS2.1, U7.39 (!CS), U8.1 (RPB9/SDA1/CTED4/PMD3/RB9)
CS3: TPCS3.1, U1.39 (!CS), U8.44 (RPB8/SCL1/CTED10/PMD4/RB8)
CS4: TPCS4.1, U2.39 (!CS), U8.43 (RPB7/CTED3/PMD5/INT0/RB7)
CS5: TPCS5.1, U3.39 (!CS), U8.21 (PGED1/AN2/C1IND/C2INB/C3IND/RPB0/PMD0/R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)
CS6: TPCS6.1, U5.39 (!CS), U8.22 (PGEC1/AN3/C1INC/C2INA/RPB1/CTED12/PMD1/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)
CS7: TPCS7.1, U8.34 (SOSCO/RPA4/T1CK/CTED9/RA4), U26.4 (CS)
CS8: JP7.1, TPCS8.1, U8.35 (TDI/RPA9/PMA9/RA9)
CS9: JP6.8, TPCS9.1, U8.38 (RPC5/PMA3/RC5)
DGND: C4.2, C9.2, C21.2, C22.2, C23.2, C39.2, C40.2, C55.2, C56.2, C77.1, C81.2, C82.2, C85.2, C86.1, C88.2, C91.2, C92.2, C111.2, C113.2, C114.2, C115.2, C117.1, C150.2, C151.2, C167.2, C168.2, C250.2, C251.2, C252.2, C253.2, C254.2, C255.2, C256.2, C257.2, C258.2, C259.2, FB1.2, FB2.2, FB3.2, FB4.2, FB5.2, FB6.2, FB7.2, FB8.2, FB9.2, FB10.2, FB11.2, FB12.2, FB13.2, FB14.2, JP4.5, JP6.2, JP7.6, R2.1, TP22.1, TP23.1, TP24.1, TP25.1, TP26.1, TP27.1, TP28.1, TP29.1, U1.31 (RESV1), U1.33 (DGND), U1.41 (DAISY_IN), U1.49 (DGND), U1.51 (DGND), U2.31 (RESV1), U2.33 (DGND), U2.41 (DAISY_IN), U2.49 (DGND), U2.51 (DGND), U3.31 (RESV1), U3.33 (DGND), U3.41 (DAISY_IN), U3.49 (DGND), U3.51 (DGND), U4.31 (RESV1), U4.33 (DGND), U4.41 (DAISY_IN), U4.49 (DGND), U4.51 (DGND), U5.31 (RESV1), U5.33 (DGND), U5.41 (DAISY_IN), U5.49 (DGND), U5.51 (DGND), U7.31 (RESV1), U7.33 (DGND), U7.41 (DAISY_IN), U7.49 (DGND), U7.51 (DGND), U8.6 (VSS_2), U8.29 (VSS_3), U8.39 (VSS), U26.9 (GND_2), U26.10 (GND_3), U26.11 (GND_4), U26.12 (GND_5), U26.13 (GND_6), U26.14 (GND_7), U26.15 (GND_8), U26.16 (GND)
DRDY1: U4.47 (!DRDY), U8.19 (PGED3/VREF+/CVREF+/AN0/C3INC/RPA0/CTED1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)
DRDY2: U7.47 (!DRDY), U8.2 (RPC6/PMA1/RC6)
DRDY3: U1.47 (!DRDY), U8.3 (RPC7/PMA0/RC7)
DRDY4: U2.47 (!DRDY), U8.4 (RPC8/PMA5/RC8)
DRDY5: U3.47 (!DRDY), U8.5 (RPC9/CTED7/PMA6/RC9)
DRDY6: U5.47 (!DRDY), U8.23 (AN4/C1INB/C2IND/RPB2/SDA2/CTED13/PMD2/C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)
DVDD: C4.1, C9.1, C21.1, C22.1, C23.1, C39.1, C40.1, C55.1, C56.1, C77.2, C81.1, C82.1, C86.2, C88.1, C91.1, C92.1, C112.2, C113.1, C117.2, C132.1, C150.1, C151.1, C167.1, C168.1, C250.1, C251.1, C252.1, C253.1, C254.1, C255.1, C256.1, C257.1, C258.1, C259.1, JP4.4, JP6.1, JP7.4, R9.2, S2.2, TP4.1, U1.48 (DVDD), U1.50 (DVDD), U1.52 (CLKSEL), U2.48 (DVDD), U2.50 (DVDD), U2.52 (CLKSEL), U3.48 (DVDD), U3.50 (DVDD), U3.52 (CLKSEL), U4.48 (DVDD), U4.50 (DVDD), U4.52 (CLKSEL), U5.48 (DVDD), U5.50 (DVDD), U5.52 (CLKSEL), U6.4 (!SD), U6.5 (V+), U7.48 (DVDD), U7.50 (DVDD), U7.52 (CLKSEL), U8.10 (VUSB3V3), U8.17 (AVDD), U8.28 (VDD_2), U8.40 (VDD), U9.1 (VOUT), U11.1 (IN), U11.3 (EN), U26.7 (VDDIO), U26.8 (VDD)
EN: JP5.6, U8.26 (AN7/RPC1/RC1)
IN1N: C103.7, RN1.6, U4.15 (IN1N)
IN1P: C103.8, RN1.5, U4.16 (IN1P)
IN2N: C103.5, RN1.8, U4.13 (IN2N)
IN2P: C103.6, RN1.7, U4.14 (IN2P)
IN3N: C104.7, RN2.6, U4.11 (IN3N)
IN3P: C104.8, RN2.5, U4.12 (IN3P)
IN4N: C104.5, RN2.8, U4.9 (IN4N)
IN4P: C104.6, RN2.7, U4.10 (IN4P)
IN5N: C106.7, RN3.6, U7.15 (IN1N)
IN5P: C106.8, RN3.5, U7.16 (IN1P)
IN6N: C106.5, RN3.8, U7.13 (IN2N)
IN6P: C106.6, RN3.7, U7.14 (IN2P)
IN7N: C107.7, RN4.6, U7.11 (IN3N)
IN7P: C107.8, RN4.5, U7.12 (IN3P)
IN8N: C107.5, RN4.8, U7.9 (IN4N)
IN8P: C107.6, RN4.7, U7.10 (IN4P)
IN9N: C108.6, RN5.6, U1.15 (IN1N)
IN9P: C108.5, RN5.5, U1.16 (IN1P)
IN10N: C108.8, RN5.8, U1.13 (IN2N)
IN10P: C108.7, RN5.7, U1.14 (IN2P)
IN11N: C109.6, RN6.6, U1.11 (IN3N)
IN11P: C109.5, RN6.5, U1.12 (IN3P)
IN12N: C109.8, RN6.8, U1.9 (IN4N)
IN12P: C109.7, RN6.7, U1.10 (IN4P)
IN13N: C110.6, RN7.6, U2.15 (IN1N)
IN13P: C110.5, RN7.5, U2.16 (IN1P)
IN14N: C110.8, RN7.8, U2.13 (IN2N)
IN14P: C110.7, RN7.7, U2.14 (IN2P)
IN15N: C126.6, RN8.6, U2.11 (IN3N)
IN15P: C126.5, RN8.5, U2.12 (IN3P)
IN16N: C126.8, RN8.8, U2.9 (IN4N)
IN16P: C126.7, RN8.7, U2.10 (IN4P)
IN17N: C127.6, RN9.6, U3.15 (IN1N)
IN17P: C127.5, RN9.5, U3.16 (IN1P)
IN18N: C127.8, RN9.8, U3.13 (IN2N)
IN18P: C127.7, RN9.7, U3.14 (IN2P)
IN19N: C128.6, RN10.6, U3.11 (IN3N)
IN19P: C128.5, RN10.5, U3.12 (IN3P)
IN20N: C128.8, RN10.8, U3.9 (IN4N)
IN20P: C128.7, RN10.7, U3.10 (IN4P)
IN21N: C129.6, RN11.6, U5.15 (IN1N)
IN21P: C129.5, RN11.5, U5.16 (IN1P)
IN22N: C129.8, RN11.8, U5.13 (IN2N)
IN22P: C129.7, RN11.7, U5.14 (IN2P)
IN23N: C130.6, RN12.6, U5.11 (IN3N)
IN23P: C130.5, RN12.5, U5.12 (IN3P)
IN24N: C130.8, RN12.8, U5.9 (IN4N)
IN24P: C130.7, RN12.7, U5.10 (IN4P)
INT1: U8.41 (RPB5/USBID/RB5), U26.6 (INT1)
MCLR': JP4.1, R1.1, U8.18 (*MCLR)
MISO: JP6.3, JP7.7, TP9.1, TP10.1, U1.43 (DOUT), U2.43 (DOUT), U3.43 (DOUT), U4.43 (DOUT), U5.43 (DOUT), U7.43 (DOUT), U8.9 (PGEC2/RPB11/D-/RB11), U26.3 (SDO)
MOSI: JP6.7, JP7.2, TP5.1, TP7.1, TP16.1, U1.34 (DIN), U2.34 (DIN), U3.34 (DIN), U4.34 (DIN), U5.34 (DIN), U7.34 (DIN), U8.20 (PGEC3/VREF-/CVREF-/AN1/RPA1/CTED2/PMD6/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), U26.2 (SDI)
unnamed: C119.1, U4.26 (VCAP4)
unnamed: C3.1, C8.1, U4.55 (VCAP3)
unnamed: C121.1, U4.30 (VCAP2)
unnamed: C101.1, U4.28 (VCAP1)
unnamed: C15.1, C16.1, U7.55 (VCAP3)
unnamed: C17.1, U7.30 (VCAP2)
unnamed: C154.1, U7.28 (VCAP1)
unnamed: CR1.2, J1.1
unnamed: C31.1, C32.1, U1.55 (VCAP3)
unnamed: C34.1, U1.30 (VCAP2)
unnamed: C102.1, U1.28 (VCAP1)
unnamed: C48.1, C49.1, U2.55 (VCAP3)
unnamed: C50.1, U2.30 (VCAP2)
unnamed: C153.1, U2.28 (VCAP1)
unnamed: C61.1, C62.1, U3.55 (VCAP3)
unnamed: C63.1, U3.30 (VCAP2)
unnamed: C122.1, U3.28 (VCAP1)
unnamed: C42.1, U1.64 (WCT)
unnamed: C74.1, C75.1, U5.55 (VCAP3)
unnamed: C76.1, U5.30 (VCAP2)
unnamed: C136.1, U5.28 (VCAP1)
unnamed: C98.1, U10.5 (NR)
unnamed: C64.2, U6.6 (CAP+)
unnamed: C64.1, U6.3 (CAP-)
unnamed: C115.1, R10.1, U8.30 (OSC1/CLKI/RPA2/RA2), XTAL1.1
unnamed: C2.2, C5.1, U4.24 (VREFP)
unnamed: C114.1, R10.2, U8.31 (OSC2/CLKO/RPA3/RA3), XTAL1.2
unnamed: C111.1, R1.2, R9.1
unnamed: C85.1, U8.7 (VCAP)
unnamed: C25.1, U7.64 (WCT)
unnamed: C10.1, U7.26 (VCAP4)
unnamed: C26.1, U1.26 (VCAP4)
unnamed: C68.1, U2.64 (WCT)
unnamed: C43.1, U2.26 (VCAP4)
unnamed: C84.1, U5.64 (WCT)
unnamed: C69.1, U5.26 (VCAP4)
unnamed: C13.2, C14.1, U7.24 (VREFP)
unnamed: C94.1, U3.64 (WCT)
unnamed: C33.1, U3.26 (VCAP4)
unnamed: C46.2, C47.1, U2.24 (VREFP)
unnamed: C72.2, C73.1, U5.24 (VREFP)
unnamed: C59.2, C60.1, U3.24 (VREFP)
unnamed: C29.2, C30.1, U1.24 (VREFP)
unnamed: C7.1, U4.64 (WCT)
PGEC: JP4.2, U8.13 (PGEC/TCK/CTED8/PMA7/RA7)
PGED: JP4.3, U8.12 (PGED/TMS/PMA10/RA10)
RAW: C87.1, CR1.1, JP5.5, TPRAW.1, U9.5 (SHDN'), U9.8 (VIN)
RESET: JP6.5, U1.36 (!RESET), U2.36 (!RESET), U3.36 (!RESET), U4.36 (!RESET), U5.36 (!RESET), U7.36 (!RESET), U8.8 (PGED2/RPB10/D+/CTED11/RB10)
RLDIN1: JP19.1, U4.62 (RLDIN)
RLDIN2: JP20.1, U7.62 (RLDIN)
RLDIN3: JP21.1, U1.62 (RLDIN)
RLDIN4: JP22.1, U2.62 (RLDIN)
RLDIN5: JP23.1, U3.62 (RLDIN)
RLDIN6: JP24.1, U5.62 (RLDIN)
RLDINV1: C54.2, JP1.1, R3.1, U4.61 (RLDINV)
RLDINV2: C24.2, JP1.2, R4.1, U7.61 (RLDINV)
RLDINV3: C41.2, JP1.3, R5.1, U1.61 (RLDINV)
RLDINV4: C67.2, JP1.4, R8.1, U2.61 (RLDINV)
RLDINV5: C93.2, JP1.5, R6.1, U3.61 (RLDINV)
RLDINV6: C83.2, JP1.6, R7.1, U5.61 (RLDINV)
RLDOUT1: C54.1, JP19.2, R3.2, U4.63 (RLDOUT)
RLDOUT2: C24.1, JP20.2, R4.2, U7.63 (RLDOUT)
RLDOUT3: C41.1, JP21.2, R5.2, U1.63 (RLDOUT)
RLDOUT4: C67.1, JP22.2, R8.2, U2.63 (RLDOUT)
RLDOUT5: C93.1, JP23.2, R6.2, U3.63 (RLDOUT)
RLDOUT6: C83.1, JP24.2, R7.2, U5.63 (RLDOUT)
RPA8: JP10.1, U8.32 (TDO/RPA8/PMA8/RA8)
RPC2: JP10.2, U8.27 (AN8/RPC2/PMA2/RC2)
RPC3: JP10.3, U8.36 (AN12/RPC3/RC3)
RPC4: JP10.4, U8.37 (RPC4/PMA4/RC4)
RXD: JP5.2, U8.11 (AN11/RPB13/CTPLS/PMRD/RB13)
SCLK: JP6.4, JP7.5, TP30.1, U1.40 (SCLK), U2.40 (SCLK), U3.40 (SCLK), U4.40 (SCLK), U5.40 (SCLK), U7.40 (SCLK), U8.14 (CVREF/AN10/C3INB/RPB14/VBUSON/SCK1/CTED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), U26.1 (SPC)
START: U1.38 (START), U2.38 (START), U3.38 (START), U4.38 (START), U5.38 (START), U7.38 (START), U8.25 (AN6/RPC0/RC0)
STATE: JP5.1
TXD: JP5.3, U8.24 (AN5/C1INA/C2INC/RTCC/RPB3/SCL2/PMWR/CNB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)
VBUS: U8.42 (VBUS)

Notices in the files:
pcb_files/final_pcb/BOM_final_pcb.csv:
"CKCL44X7R1H102M085AACKCL44_TDK-L";"CKCL44X7R1H102M085AACKCL44_TDK-L";"CKCL44_TDK-L";"";"";"Copyright (C) 2023 Ultra Librarian. All rights reserved.";"";"";"";"";"";"CKCL44X7R1H102M085AA";"TDK";"";"";"";"";"";"";"";"";"";"";"";"";"";"";"";"";"";"";"";"";
"BAT85,113DO-34_NEX";"BAT85,113DO-34_NEX";"DO-34_NEX";"";"";"Copyright (C) 2023 Ultra Librarian. All rights reserved.";"";"";"";"";"";"BAT85,113";"Nexperia";"";"";"";"";"";"";"";"";"";"";"";"";"";"";"";"";"";"";"";"";
